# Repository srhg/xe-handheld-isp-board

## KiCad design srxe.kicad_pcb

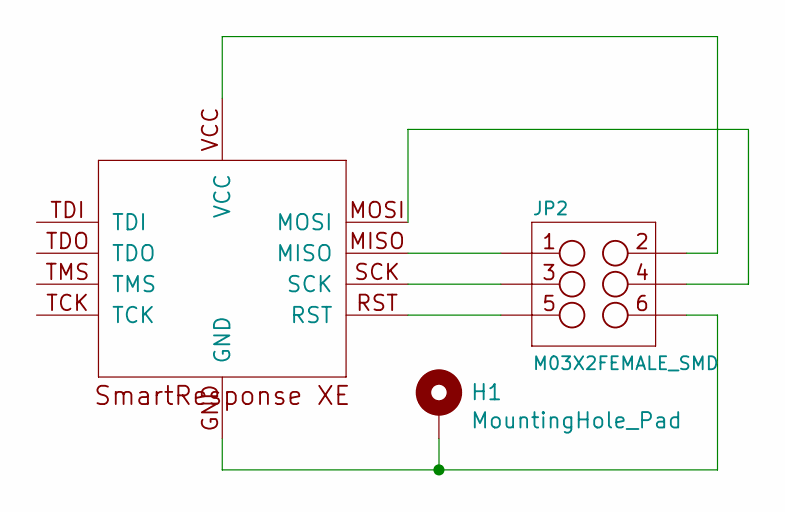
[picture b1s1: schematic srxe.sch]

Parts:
H1: MountingHole_Pad; MountingHole_3.2mm_M3
JP2: M03X2FEMALE_SMD; 2X3_SMD
U$1: SMARTRESPONSEXE; SMARTRESPONSEXEPOGO

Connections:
unnamed: H1.1, JP2.6, U$1.GND
unnamed: JP2.1, U$1.MISO
unnamed: JP2.2, U$1.VCC
unnamed: JP2.3, U$1.SCK
unnamed: JP2.4, U$1.MOSI
unnamed: JP2.5, U$1.RST

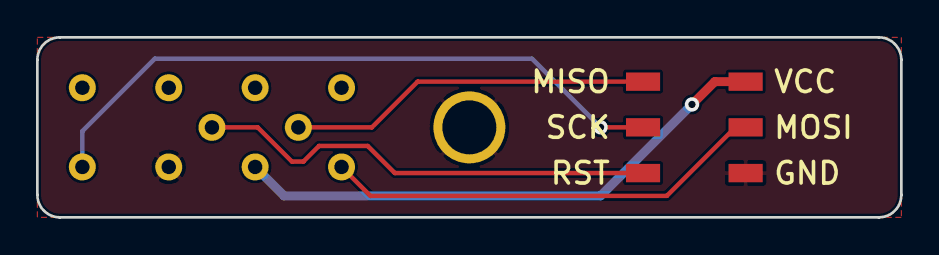
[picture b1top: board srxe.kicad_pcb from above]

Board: 2 copper layers, 48.0 x 10.0 mm, 3 parts (0 on the bottom side), 6 nets.

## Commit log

2020-01-29 tighten tollerances
2020-01-29 align grid
2020-01-29 mark v0.2
2020-01-29 add soldering jig sketchup design file
2020-01-29 move model to origin
2020-03-20 update soldering jig
